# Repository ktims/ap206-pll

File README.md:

View this project on [CADLAB.io](https://cadlab.io/project/2304). 

# ap206-pll

This is a "modern" (ie. using available parts) replacement for the AP3601 PLL board found in the Akai AP-306 turntable. It can be added to an Akai AP-206 turntable to add Quartz Lock functionality.

## Design notes

The original Akai design used a 4.42368MHz crystal divided down by a flip-flop and programmable counter to 20Hz or 27Hz depending on selected speed. This is then compared with the conditioned feedback signal from the motor driver by PLL IC. See the Service Manual and schematic for more details.

This design uses an AVR ATtiny to divide down the clock in one step rather than using discrete logic. The programmable divider in the original design is no longer available, and a suitable replacement is not present in the 74xx or 4000 series of devices, and in addition the oddball crystal frequency is no longer available. Rather than using a bunch of extra logic, the ATtiny was used. The frequencies generated are 20Hz (33-1/3) and 27Hz (45) by dividing the 11.0592MHz clock by 552960 or 409600 using the PWM hardware. Likewise the PLL IC used is no longer available and was replaced with a 'modern' 4046. The circuit is otherwise basically identical to the original design.

**Note: 74xx variants *cannot* be used in any position. Original 4000 series CMOS variants must be used due to the 7.5V supply voltage and input signals from the motor.**

## Installation

It has been tested and works well, but installation requires some understanding of the design and will not be supported beyond the below notes. 

* Consult the (included) service manual to determine pin numbers on the DD PCB for where to attach to the new PCB
* Some existing connections must be broken and replaced with the new circuits. Most significantly, the AP-206 has two speed pots, while the AP-306 has one. You must disconnect one of them and rewire per the AP-306 (see the wiring diagram on p. 22 of the service manual which shows both models). Note that SW903 which was a discrete switch on the AP-306 is on the PCB here, so those connections go to the PCB as below.

### Connections
 
 ap206-pll label | connection 
 --------------- | ---------- 
 7.5Vin          | DD Board Pin 20
 GNDin           | DD Board Pin 21
 FGin            | DD Board Pin 16
 SW-1            | Speed Switch 33 position (unused side)
 SW-COM          | Speed Switch Common (unused side)
 SW-2            | Speed Switch 45 position (unused side)
| | |
 13              | DD Board Pin 13
 12              | DD Board Pin 12
 SVR             | Common of the 'speed' pot (keep only one)
 SSW             | Common of the speed switch (prepopulated side)
 19              | DD Board Pin 19

## Adjustment
You will need to adjust the two speed pots on the DD board (VR2, VR3) for a reasonably close speed after installation, or the PLL will not be able to lock. Once speeds are adjusted correctly, adjust RV1 until lock is achieved. No lock indicator is included, but should be obvious. For verification, pins 3 & 14 of U7 can be scoped; they should be stable in relative phase when lock is achieved.

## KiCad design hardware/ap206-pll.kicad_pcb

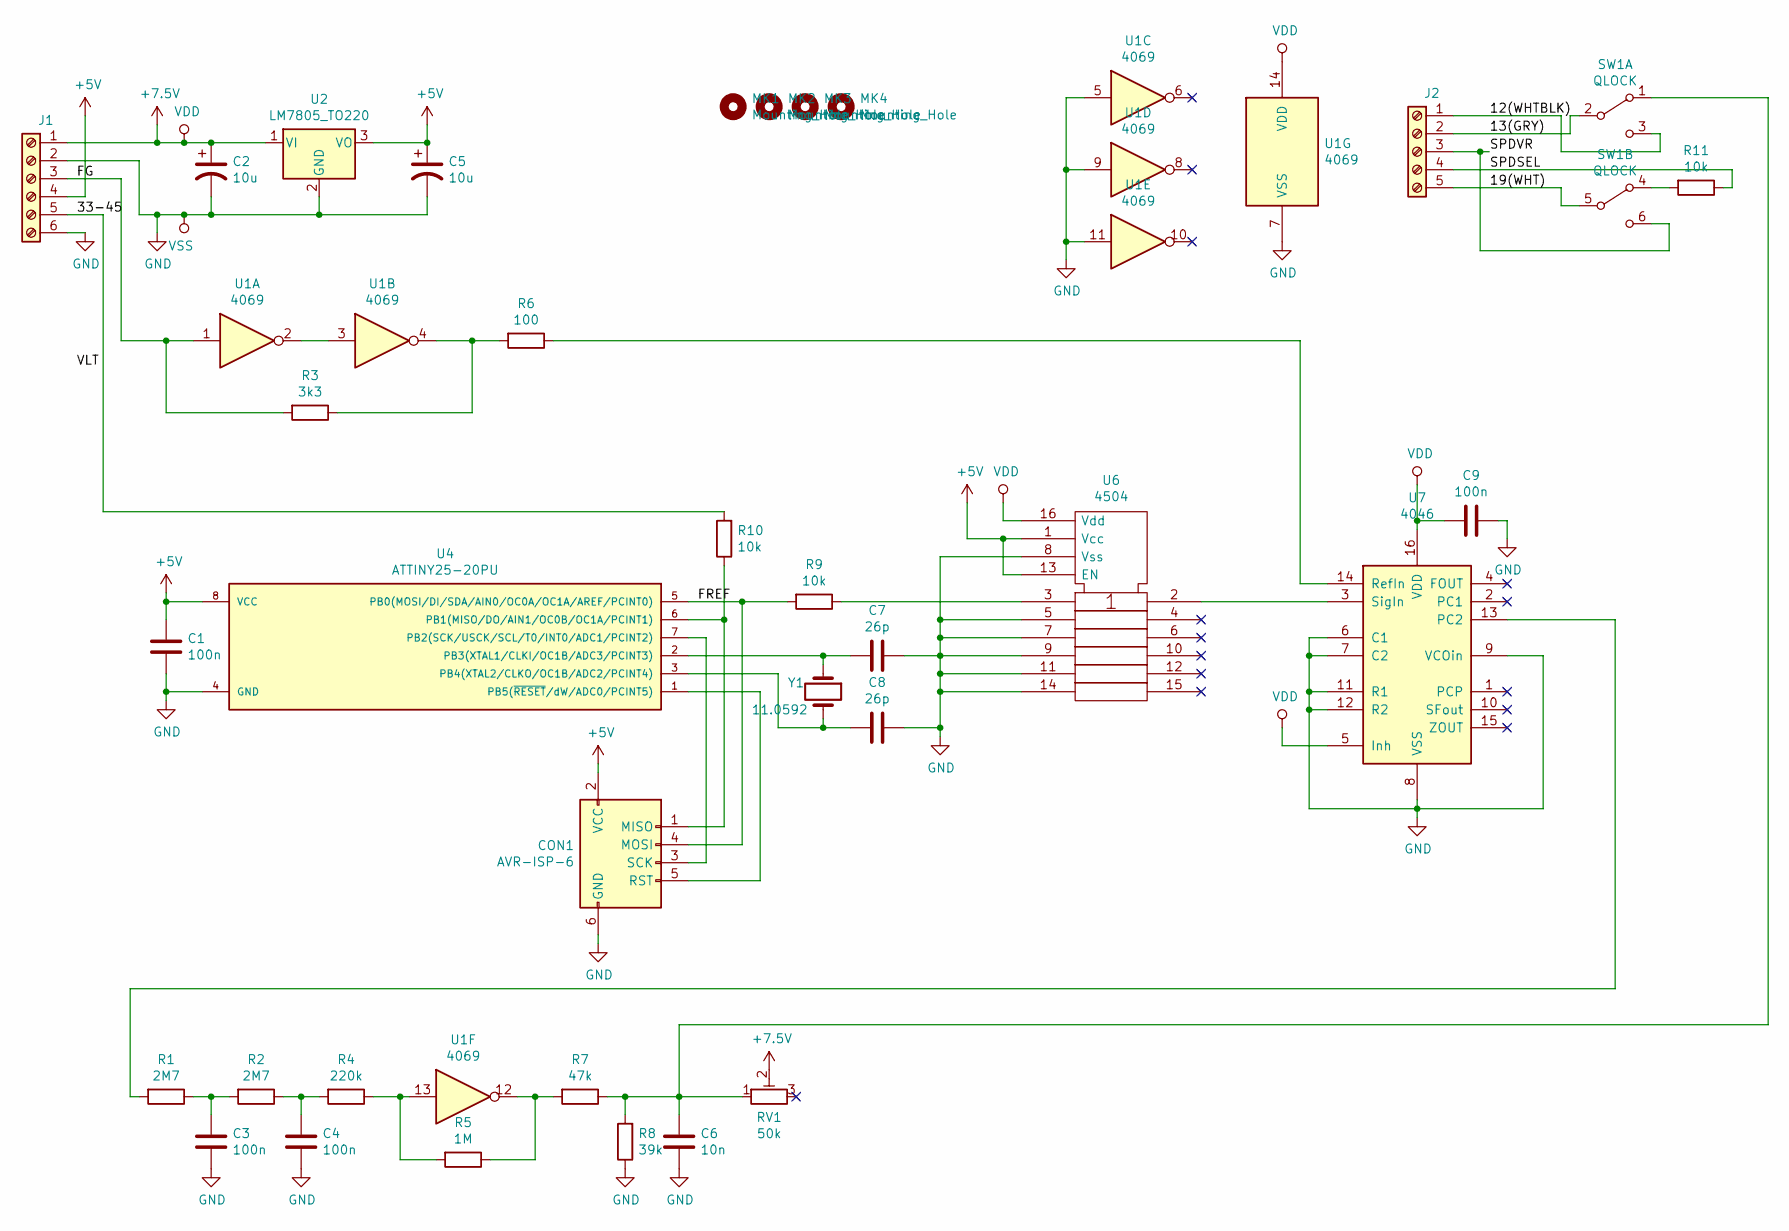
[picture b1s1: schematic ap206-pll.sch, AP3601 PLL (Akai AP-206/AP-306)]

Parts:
C1, C3, C4, C9: 100n; C_Disc_D5.1mm_W3.2mm_P5.00mm
C2, C5: 10u; CP_Radial_D5.0mm_P2.50mm
C6: 10n; C_Disc_D5.1mm_W3.2mm_P5.00mm
C7, C8: 26p; C_Disc_D5.1mm_W3.2mm_P5.00mm
CON1: AVR-ISP-6; IDC-Header_2x03_P2.54mm_Vertical
J1: Screw_Terminal_01x06; TerminalBlock_Phoenix_PT-1,5-6-3.5-H_1x06_P3.50mm_Horizontal; Part# 1985001
J2: Screw_Terminal_01x05; TerminalBlock_Phoenix_PT-1,5-5-3.5-H_1x05_P3.50mm_Horizontal; Part# 1989777
MK1, MK2, MK3, MK4: Mounting_Hole; MountingHole_4mm
R1, R2: 2M7; R_Axial_DIN0207_L6.3mm_D2.5mm_P7.62mm_Horizontal
R3: 3k3; R_Axial_DIN0207_L6.3mm_D2.5mm_P7.62mm_Horizontal
R4: 220k; R_Axial_DIN0207_L6.3mm_D2.5mm_P7.62mm_Horizontal
R5: 1M; R_Axial_DIN0207_L6.3mm_D2.5mm_P7.62mm_Horizontal
R6: 100; R_Axial_DIN0207_L6.3mm_D2.5mm_P7.62mm_Horizontal
R7: 47k; R_Axial_DIN0207_L6.3mm_D2.5mm_P7.62mm_Horizontal
R8: 39k; R_Axial_DIN0207_L6.3mm_D2.5mm_P7.62mm_Horizontal
R9, R10, R11: 10k; R_Axial_DIN0207_L6.3mm_D2.5mm_P7.62mm_Horizontal
RV1: 50k; Potentiometer_Bourns_3386P_Vertical
SW1: QLOCK; SW_CuK_JS202011CQN_DPDT_Straight
U1: 4069; DIP-14_W7.62mm
U2: LM7805_TO220; TO-220-3_Vertical
U4: ATTINY25-20PU; DIP-8_W7.62mm
U6: 4504; DIP-16_W7.62mm
U7: 4046; DIP-16_W7.62mm
Y1: 11.0592; Crystal_HC49-U_Vertical

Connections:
+5V: C1.1, C5.1, CON1.2 (VCC), J1.4, U2.3 (VO), U4.8 (VCC), U6.1 (Vcc), U6.13 (EN)
+7.5V: C2.1, C9.2, J1.1, RV1.2, U1.14 (VDD), U2.1 (VI), U6.16 (Vdd), U7.5 (Inh), U7.16 (VDD)
/12(WHTBLK): J2.1, SW1.3 (C)
/13(GRY): J2.2, SW1.2 (B)
/19(WHT): J2.5, SW1.5 (B)
/33-45: J1.5, R10.2
/FG: J1.3, R3.2, U1.1
/FREF: CON1.4 (MOSI), R9.2, U4.5 (PB0(MOSI/DI/SDA/AIN0/OC0A/OC1A/AREF/PCI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)
/SPDSEL: J2.4, R11.1
/SPDVR: J2.3, SW1.6 (C)
GND: C1.2, C2.2, C3.2, C4.2, C5.2, C6.2, C7.1, C8.2, C9.1, CON1.6 (GND), J1.2, J1.6, R8.1, U1.5, U1.7 (VSS), U1.9, U1.11, U2.2 (GND), U4.4 (GND), U6.5, U6.7, U6.8 (Vss), U6.9, U6.11, U6.14, U7.6 (C1), U7.7 (C2), U7.8 (VSS), U7.9 (VCOin), U7.11 (R1), U7.12 (R2)
unnamed: C3.1, R1.1, R2.2
unnamed: C4.1, R2.1, R4.2
unnamed: C6.1, R7.1, R8.2, RV1.1, SW1.1 (A)
unnamed: C7.2, U4.2 (PB3(XTAL1/CLKI/OC1B/ADC3/PCINT3)), Y1.1
unnamed: C8.1, U4.3 (PB4(XTAL2/CLKO/OC1B/ADC2/PCINT4)), Y1.2
unnamed: CON1.1 (MISO), R10.1, U4.6 (PB1(MISO/DO/AIN1/OC0B/OC1A/PCINT1))
unnamed: CON1.3 (SCK), U4.7 (PB2(SCK/USCK/SCL/T0/INT0/ADC1/PCINT2))
unnamed: CON1.5 (RST), U4.1 (PB5(~RESET~/dW/ADC0/PCINT5))
unnamed: R1.2, U7.13 (PC2)
unnamed: R3.1, R6.2, U1.4
unnamed: R4.1, R5.2, U1.13
unnamed: R5.1, R7.2, U1.12
unnamed: R6.1, U7.14 (RefIn)
unnamed: R9.1, U6.3
unnamed: R11.2, SW1.4 (A)
unnamed: U1.2, U1.3
unnamed: U6.2, U7.3 (SigIn)

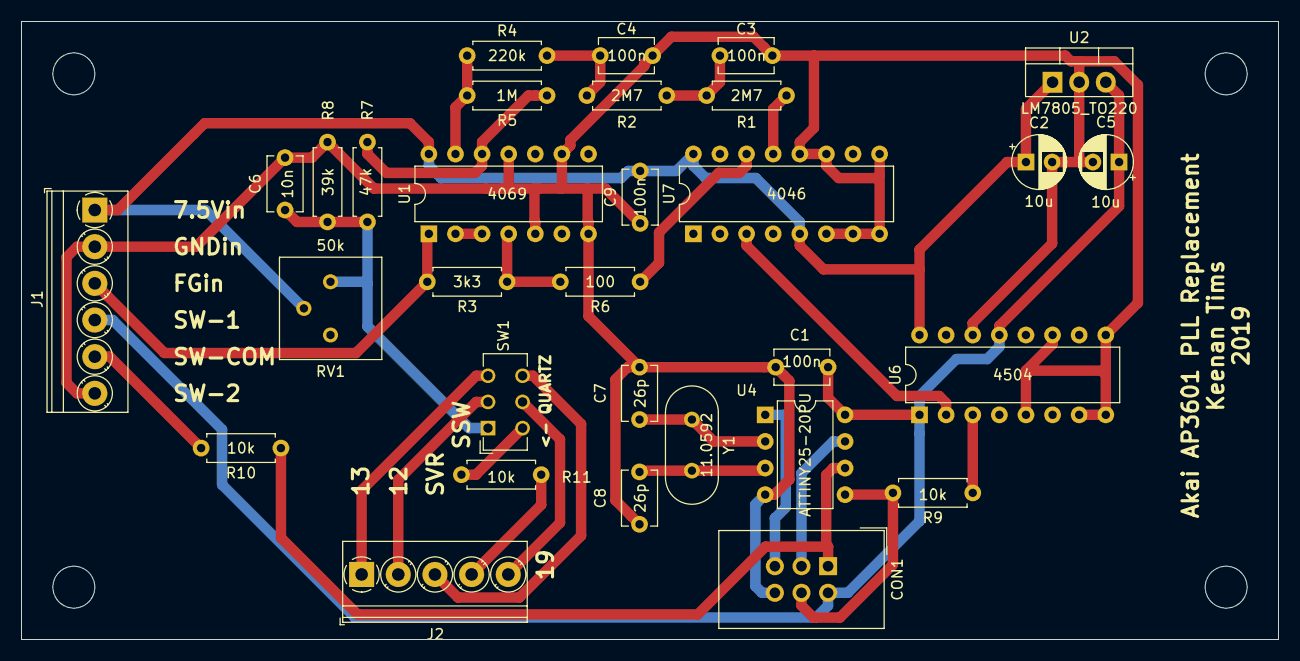
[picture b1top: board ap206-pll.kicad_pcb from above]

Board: 2 copper layers, 120.0 x 59.0 mm, 35 parts (0 on the bottom side), 28 nets.

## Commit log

2019-08-05 Initial commit - rev1 to fab
2019-10-12 Initial tested and working version, with fixes
2019-10-12 Add README Fix pin label
2019-11-18 Add documentation and symbol cache (for CADLAB)
2019-11-18 Backlink to CADLAB.io has been added.
